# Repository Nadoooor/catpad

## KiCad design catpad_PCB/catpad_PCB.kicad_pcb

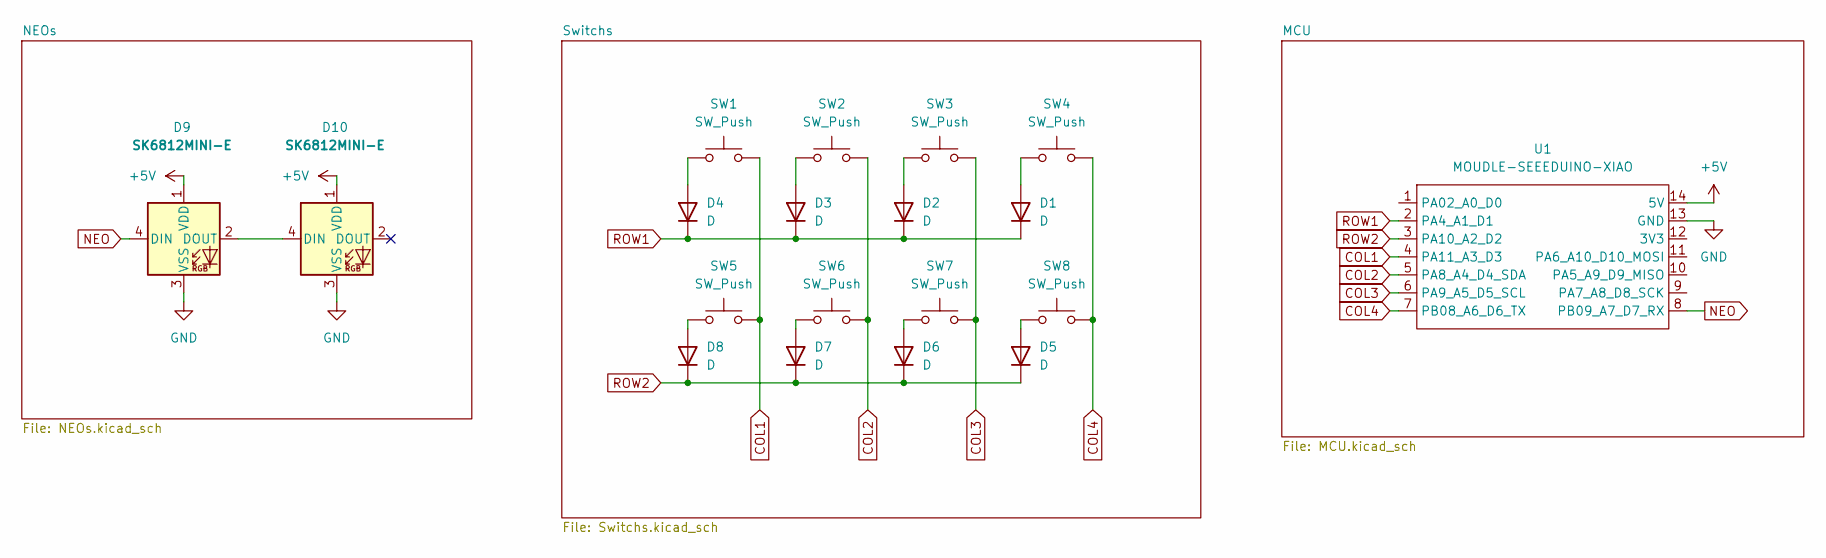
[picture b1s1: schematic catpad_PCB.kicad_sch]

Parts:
D1, D2, D3, D4, D5, D6, D7, D8: D; D_DO-35_SOD27_P7.62mm_Horizontal
D9, D10: SK6812MINI-E; SK6812MINI-E_fixed
SW1, SW2, SW3, SW4, SW5, SW6, SW7, SW8: SW_Push; SW_Cherry_MX_1.00u_PCB_With_3D
U1: MOUDLE-SEEEDUINO-XIAO; XIAO-Generic-Hybrid-14P-2.54-21X17.8MM

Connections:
+5V: D9.1 (VDD), D10.1 (VDD), U1.14 (5V)
COL1: SW1.2, SW5.2, U1.4 (PA11_A3_D3)
COL2: SW2.2, SW6.2, U1.5 (PA8_A4_D4_SDA)
COL3: SW3.2, SW7.2, U1.6 (PA9_A5_D5_SCL)
COL4: SW4.2, SW8.2, U1.7 (PB08_A6_D6_TX)
GND: D9.3 (VSS), D10.3 (VSS), U1.13 (GND)
NEO: D9.4 (DIN), U1.8 (PB09_A7_D7_RX)
unnamed: D1.2 (A), SW4.1
unnamed: D2.2 (A), SW3.1
unnamed: D3.2 (A), SW2.1
unnamed: D4.2 (A), SW1.1
unnamed: D5.2 (A), SW8.1
unnamed: D6.2 (A), SW7.1
unnamed: D7.2 (A), SW6.1
unnamed: D8.2 (A), SW5.1
unnamed: D9.2 (DOUT), D10.4 (DIN)
ROW1: D1.1 (K), D2.1 (K), D3.1 (K), D4.1 (K), U1.2 (PA4_A1_D1)
ROW2: D5.1 (K), D6.1 (K), D7.1 (K), D8.1 (K), U1.3 (PA10_A2_D2)

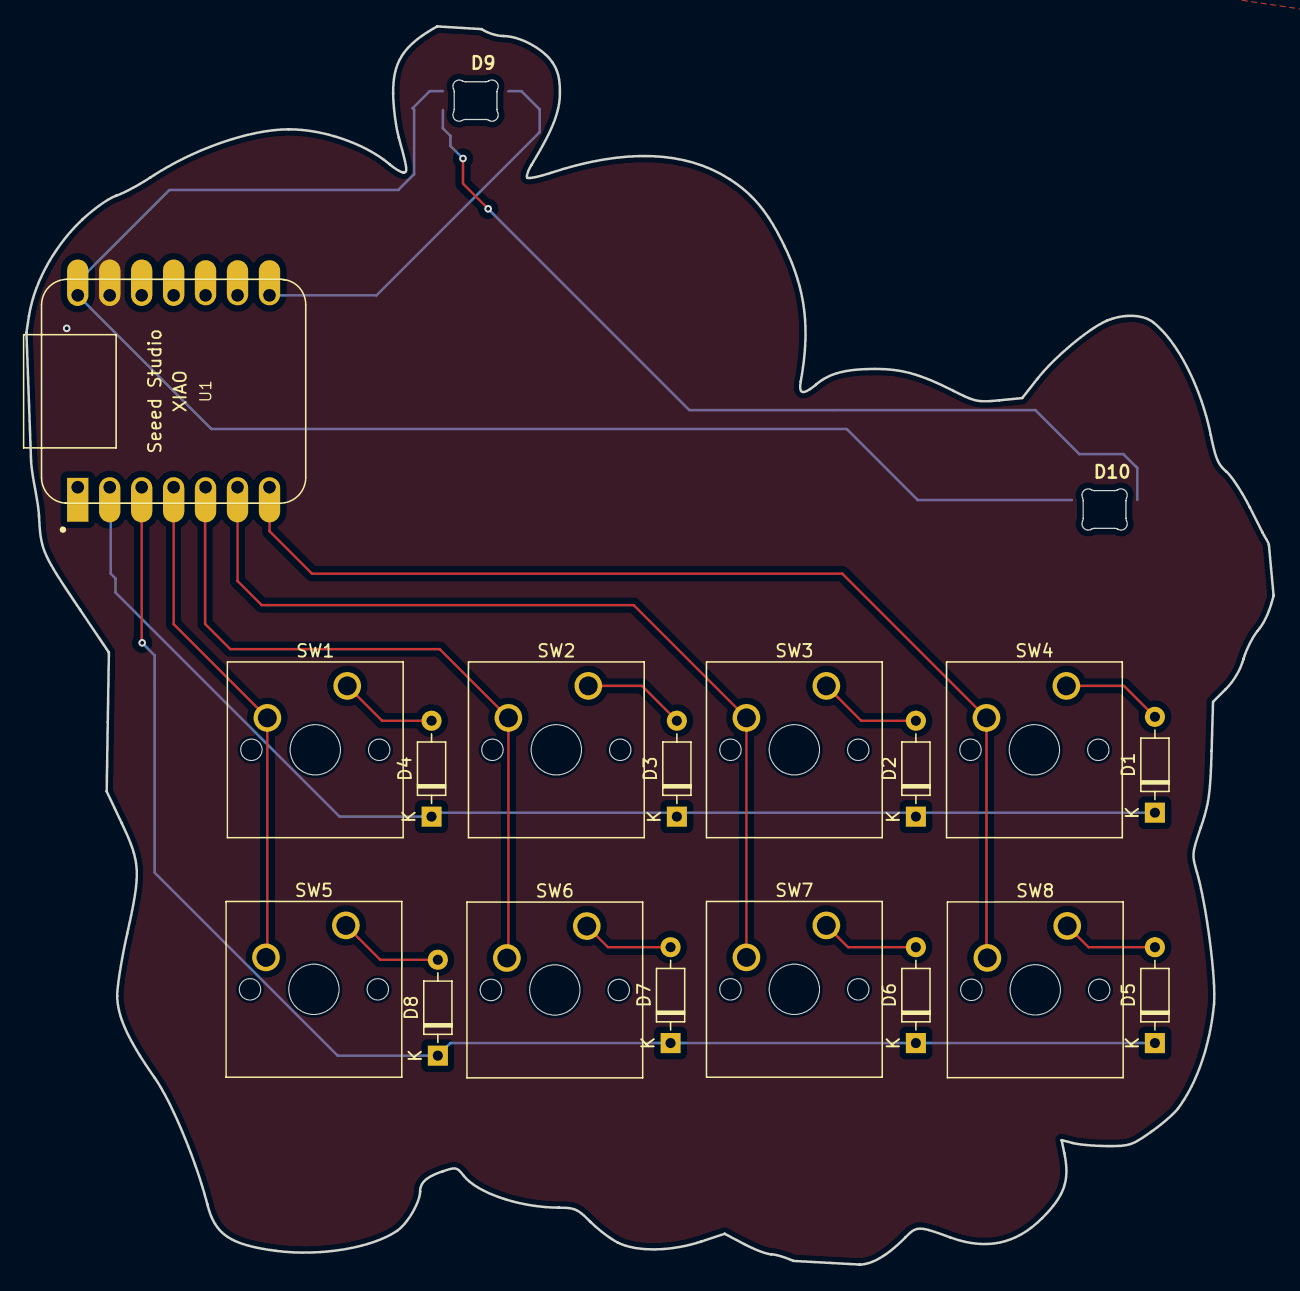
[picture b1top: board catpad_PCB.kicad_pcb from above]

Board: 2 copper layers, 99.1 x 98.4 mm, 19 parts (0 on the bottom side), 18 nets.
